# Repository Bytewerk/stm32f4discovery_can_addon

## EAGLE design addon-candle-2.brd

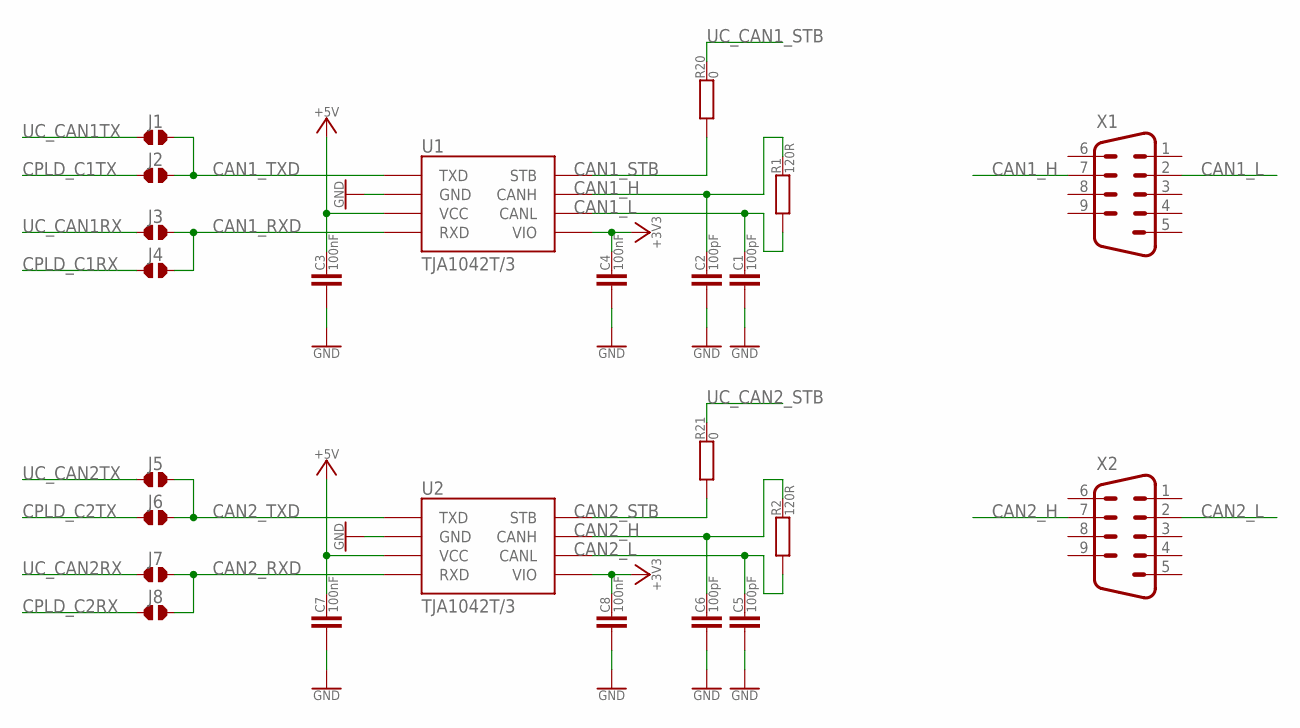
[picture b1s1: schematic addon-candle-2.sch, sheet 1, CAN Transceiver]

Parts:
C1, C2, C5, C6: 100pF; C0603
C3, C4, C7, C8: 100nF; C0603
J1, J2, J3, J4, J5, J6, J7, J8: JUMPER-2_10B; JMP2-1B
R1, R2: 120R; R0603
R20, R21: 0; R0603
U1, U2: TJA1042T/3; SO08
X1, X2: M09-182; 182-009-MALE

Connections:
+3V3: C4.2, C8.2, U1.5 (VIO), U2.5 (VIO); also elsewhere on the board
+5V: C3.2, C7.2, U1.3 (VCC), U2.3 (VCC); also elsewhere on the board
CAN1_H: C2.2, R1.2, U1.7 (CANH), X1.7
CAN1_L: C1.2, R1.1, U1.6 (CANL), X1.2
CAN1_RXD: J3.1, J4.1, U1.4 (RXD)
CAN1_STB: R20.1, U1.8 (STB)
CAN1_TXD: J1.1, J2.1, U1.1 (TXD)
CAN2_H: C6.2, R2.2, U2.7 (CANH), X2.7
CAN2_L: C5.2, R2.1, U2.6 (CANL), X2.2
CAN2_RXD: J7.1, J8.1, U2.4 (RXD)
CAN2_STB: R21.1, U2.8 (STB)
CAN2_TXD: J5.1, J6.1, U2.1 (TXD)
CPLD_C1RX: J4.2; also elsewhere on the board
CPLD_C1TX: J2.2; also elsewhere on the board
CPLD_C2RX: J8.2; also elsewhere on the board
CPLD_C2TX: J6.2; also elsewhere on the board
GND: C1.1, C2.1, C3.1, C4.1, C5.1, C6.1, C7.1, C8.1, U1.2 (GND), U2.2 (GND); also elsewhere on the board
UC_CAN1RX: J3.2; also elsewhere on the board
UC_CAN1TX: J1.2; also elsewhere on the board
UC_CAN1_STB: R20.2; also elsewhere on the board
UC_CAN2RX: J7.2; also elsewhere on the board
UC_CAN2TX: J5.2; also elsewhere on the board
UC_CAN2_STB: R21.2; also elsewhere on the board

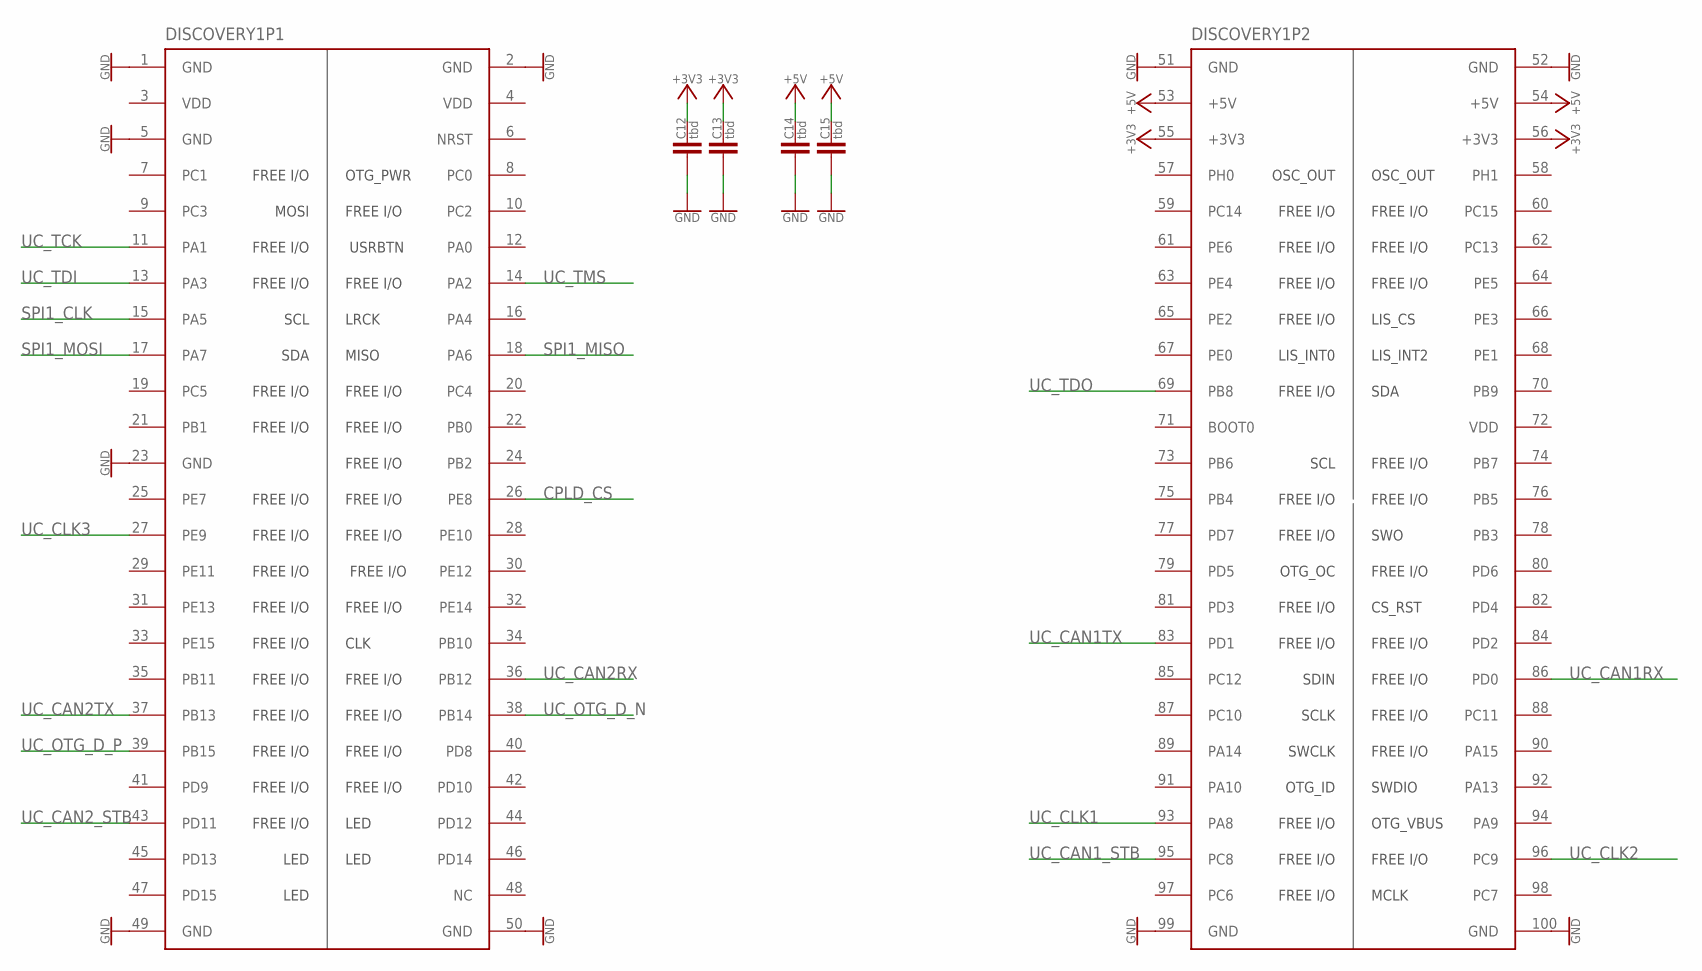
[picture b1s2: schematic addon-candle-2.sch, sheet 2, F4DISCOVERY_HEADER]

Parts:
C12, C13, C14, C15: tbd; C1206
DISCOVERY1: STM32F4DISCOVERY

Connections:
+3V3: C12.2, C13.2, DISCOVERY1.55 (+3V3), DISCOVERY1.56 (+3V3); also elsewhere on the board
+5V: C14.2, C15.2, DISCOVERY1.53 (+5V), DISCOVERY1.54 (+5V); also elsewhere on the board
CPLD_CS: DISCOVERY1.26 (PE8); also elsewhere on the board
GND: C12.1, C13.1, C14.1, C15.1, DISCOVERY1.1 (GND), DISCOVERY1.2 (GND), DISCOVERY1.5 (GND), DISCOVERY1.23 (GND), DISCOVERY1.49 (GND), DISCOVERY1.50 (GND), DISCOVERY1.51 (GND), DISCOVERY1.52 (GND), DISCOVERY1.99 (GND), DISCOVERY1.100 (GND); also elsewhere on the board
SPI1_CLK: DISCOVERY1.15 (PA5); also elsewhere on the board
SPI1_MISO: DISCOVERY1.18 (PA6); also elsewhere on the board
SPI1_MOSI: DISCOVERY1.17 (PA7); also elsewhere on the board
UC_CAN1RX: DISCOVERY1.86 (PD0); also elsewhere on the board
UC_CAN1TX: DISCOVERY1.83 (PD1); also elsewhere on the board
UC_CAN1_STB: DISCOVERY1.95 (PC8); also elsewhere on the board
UC_CAN2RX: DISCOVERY1.36 (PB12); also elsewhere on the board
UC_CAN2TX: DISCOVERY1.37 (PB13); also elsewhere on the board
UC_CAN2_STB: DISCOVERY1.43 (PD11); also elsewhere on the board
UC_CLK1: DISCOVERY1.93 (PA8); also elsewhere on the board
UC_CLK2: DISCOVERY1.96 (PC9); also elsewhere on the board
UC_CLK3: DISCOVERY1.27 (PE9); also elsewhere on the board
UC_OTG_D_N: DISCOVERY1.38 (PB14); also elsewhere on the board
UC_OTG_D_P: DISCOVERY1.39 (PB15); also elsewhere on the board
UC_TCK: DISCOVERY1.11 (PA1); also elsewhere on the board
UC_TDI: DISCOVERY1.13 (PA3); also elsewhere on the board
UC_TDO: DISCOVERY1.69 (PB8); also elsewhere on the board
UC_TMS: DISCOVERY1.14 (PA2); also elsewhere on the board

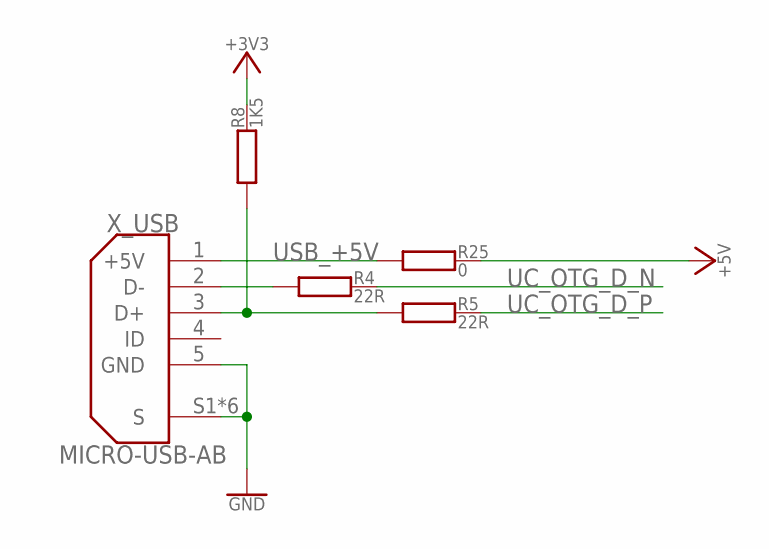
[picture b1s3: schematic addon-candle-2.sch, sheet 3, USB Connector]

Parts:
R4, R5: 22R; R0603
R8: 1K5; R0603
R25: 0; R0603
X_USB: MICRO-USB-AB; ZX62-B-5PA(11)

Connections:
+3V3: R8.2; also elsewhere on the board
+5V: R25.2; also elsewhere on the board
GND: X_USB.5 (GND), X_USB.S1 (S), X_USB.S2 (S), X_USB.S3 (S), X_USB.S4 (S), X_USB.S5 (S), X_USB.S6 (S); also elsewhere on the board
unnamed: R4.1, X_USB.2 (D-)
unnamed: R5.1, R8.1, X_USB.3 (D+)
UC_OTG_D_N: R4.2; also elsewhere on the board
UC_OTG_D_P: R5.2; also elsewhere on the board
USB_+5V: R25.1, X_USB.1 (+5V)

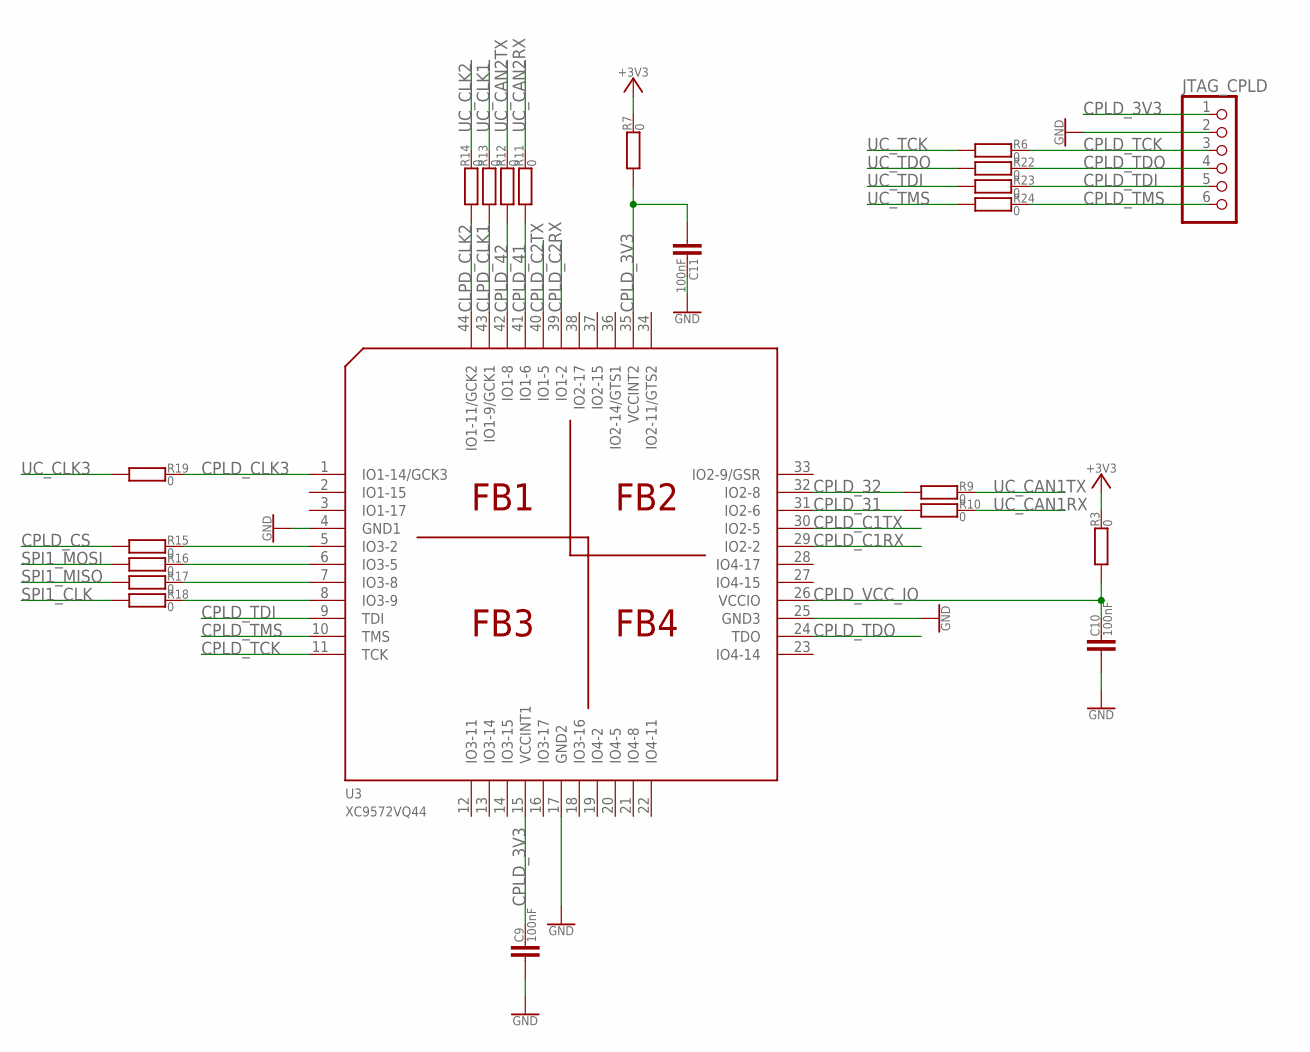
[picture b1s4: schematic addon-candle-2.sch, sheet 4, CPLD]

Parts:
C9, C10, C11: 100nF; C0603
JTAG_CPLD: PINHD-1X6; 1X06
R3, R6, R7, R9, R10, R11, R12, R13, R14, R15, R16, R17, R18, R19, R22, R23, R24: 0; R0603
U3: XC9572VQ44; VQ44

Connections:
+3V3: R3.2, R7.2; also elsewhere on the board
CLPD_CLK1: R13.1, U3.43 (IO1-9/GCK1)
CLPD_CLK2: R14.1, U3.44 (IO1-11/GCK2)
CPLD_3V3: C9.2, C11.1, JTAG_CPLD.1, R7.1, U3.15 (VCCINT1), U3.35 (VCCINT2)
CPLD_31: R10.1, U3.31 (IO2-6)
CPLD_32: R9.1, U3.32 (IO2-8)
CPLD_41: R11.1, U3.41 (IO1-6)
CPLD_42: R12.1, U3.42 (IO1-8)
CPLD_C1RX: U3.29 (IO2-2); also elsewhere on the board
CPLD_C1TX: U3.30 (IO2-5); also elsewhere on the board
CPLD_C2RX: U3.39 (IO1-2); also elsewhere on the board
CPLD_C2TX: U3.40 (IO1-5); also elsewhere on the board
CPLD_CLK3: R19.2, U3.1 (IO1-14/GCK3)
CPLD_CS: R15.1; also elsewhere on the board
CPLD_TCK: JTAG_CPLD.3, R6.2, U3.11 (TCK)
CPLD_TDI: JTAG_CPLD.5, R23.2, U3.9 (TDI)
CPLD_TDO: JTAG_CPLD.4, R22.2, U3.24 (TDO)
CPLD_TMS: JTAG_CPLD.6, R24.2, U3.10 (TMS)
CPLD_VCC_IO: C10.2, R3.1, U3.26 (VCCIO)
GND: C9.1, C10.1, C11.2, JTAG_CPLD.2, U3.4 (GND1), U3.17 (GND2), U3.25 (GND3); also elsewhere on the board
unnamed: R15.2, U3.5 (IO3-2)
unnamed: R16.2, U3.6 (IO3-5)
unnamed: R17.2, U3.7 (IO3-8)
unnamed: R18.2, U3.8 (IO3-9)
SPI1_CLK: R18.1; also elsewhere on the board
SPI1_MISO: R17.1; also elsewhere on the board
SPI1_MOSI: R16.1; also elsewhere on the board
UC_CAN1RX: R10.2; also elsewhere on the board
UC_CAN1TX: R9.2; also elsewhere on the board
UC_CAN2RX: R11.2; also elsewhere on the board
UC_CAN2TX: R12.2; also elsewhere on the board
UC_CLK1: R13.2; also elsewhere on the board
UC_CLK2: R14.2; also elsewhere on the board
UC_CLK3: R19.1; also elsewhere on the board
UC_TCK: R6.1; also elsewhere on the board
UC_TDI: R23.1; also elsewhere on the board
UC_TDO: R22.1; also elsewhere on the board
UC_TMS: R24.1; also elsewhere on the board

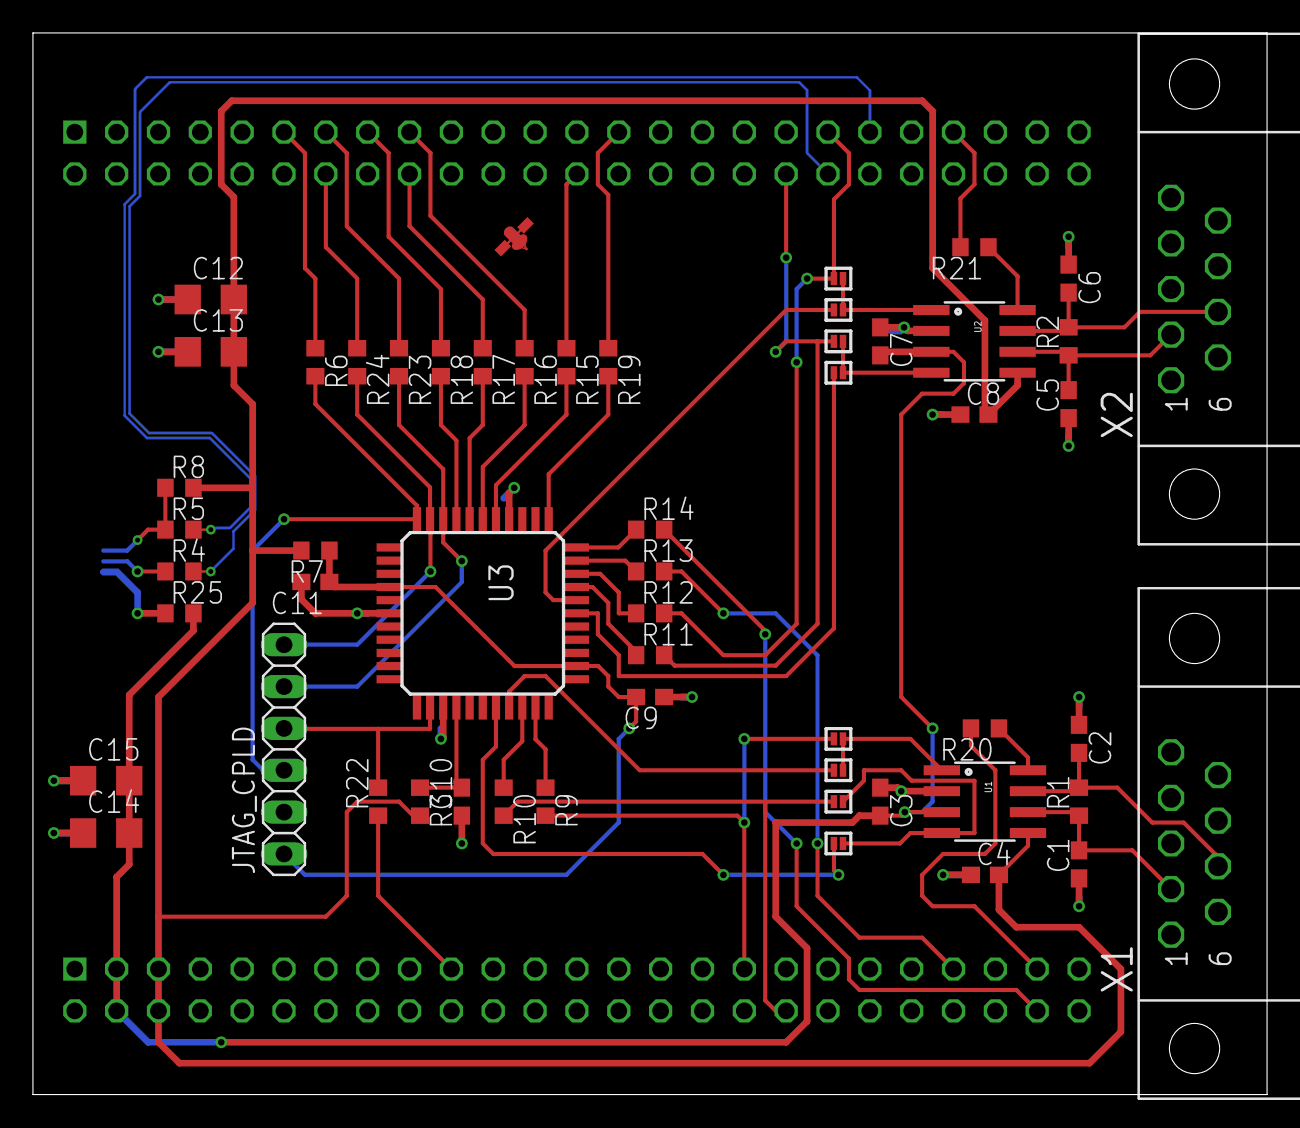
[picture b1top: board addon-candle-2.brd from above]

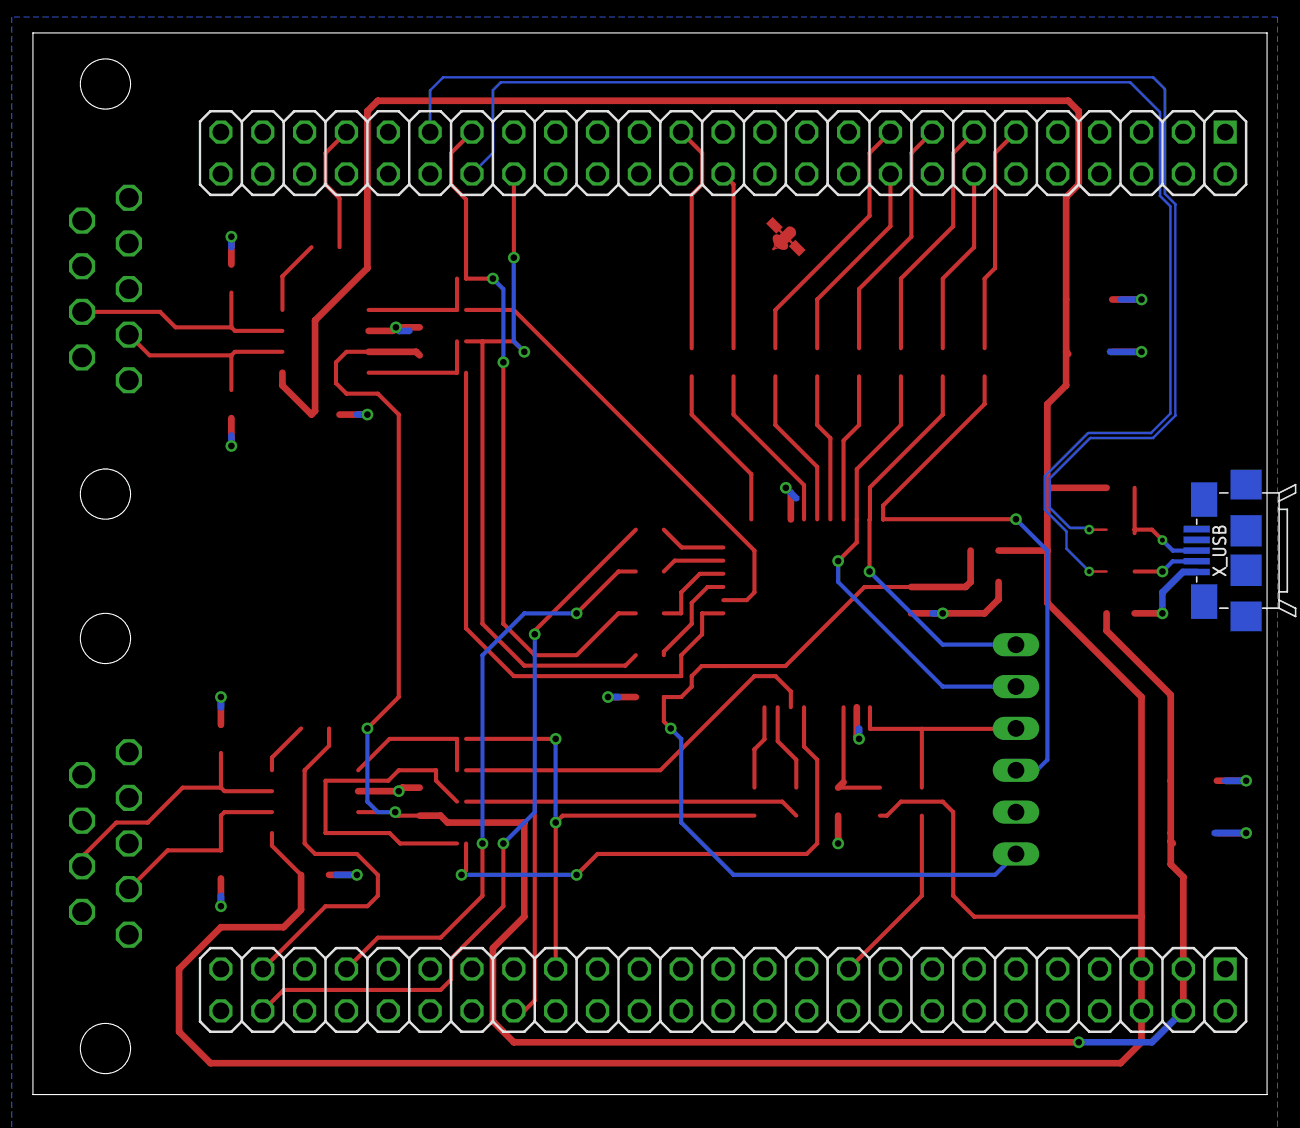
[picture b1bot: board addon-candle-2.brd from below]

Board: 2 copper layers, 74.9 x 64.4 mm, 57 parts (2 on the bottom side), 56 nets.

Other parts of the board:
U$18: BYTEWERK-LOGO

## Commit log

2015-07-28 initial checkin

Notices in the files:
parts and their libraries:
bytewerk-con: Creative Commons 3.0 CC-BY-SA
bytewerk-jumper: CC-BY-SA v4.0
